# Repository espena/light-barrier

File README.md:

# Light barrier
Garage door light barrier. KiCad project with schematics and PCB layout. This project is shared under GNU general public license version 3, and is provided "as is", with no warranties what so ever. Use this material completely at your own risk.

## Transmitter circuit

| Component ID  | Type           | Description                    | Value  |
| ------------- |:---------------|:-------------------------------| ------:|
|  C1           | Capacitor      | Radial electrolytic, 10V       | 1000µF |
|  C2           | Capacitor      | Monolithic Ceramic Chip        |  470pF |
|  C3           | Capacitor      | Monolithic Ceramic Chip        |  100nF |
|  C4           | Capacitor      | Monolithic Ceramic Chip        |  100nF |
|  C5           | Capacitor      | Monolithic Ceramic Chip        |  100nF |
|  D1           | Diode          | 1N4001, 50V                    |     -  |
|  D2           | LED            | Green, 5mm                     |     -  |
|  D3           | IR-LED         | TSAL 6100                      |     -  |
|  J1           | Terminal block | KF128 2-pin, 5 mm pitch        |     -  |
| JP1           | Jumper         | 1x2 pin header with jumper     |     -  |
|  Q1           | Transistor     | BC338 NPN BJT                  |     -  |
|  R1           | Resistor       | Metal film, 1% tolerance       |    1kΩ |
|  R2           | Resistor       | Metal film, 1% tolerance       |   24kΩ |
|  R3           | Resistor       | Metal film, 1% tolerance       |  120kΩ |
|  R4           | Resistor       | Metal film, 1% tolerance       |   22kΩ |
|  R5           | Resistor       | Metal film, 1% tolerance       |  680kΩ |
|  R6           | Resistor       | Metal film, 1% tolerance       |   10kΩ |
|  R7           | Resistor       | Metal film, 1% tolerance       |  100kΩ |
|  R8           | Resistor       | Metal film, 1% tolerance       |   10Ω  |
| RV1           | Potentiometer  | Cermet 25-turn 3296W-1         |   10kΩ |
|  U1           | IC             | TLC555 timer circuit           |     -  |
|  U2           | IC             | TLC555 timer circuit           |     -  |

PCB layout for the transmitter is shared via
[OSH Park](https://oshpark.com/shared_projects/Knkobcg6)

## Receiver circuit

| Component ID  | Type           | Description                    | Value  |
| ------------- |:---------------|:-------------------------------| ------:|
|  C1           | Capacitor      | Radial electrolytic            |   47µF |
|  C2           | Capacitor      | Monolithic Ceramic Chip        |  100nF |
|  C3           | Capacitor      | Radial electrolytic            |   10µF |
|  C4           | Capacitor      | Monolithic Ceramic Chip        |  100nF |
|  C5           | Capacitor      | Monolithic Ceramic Chip        |  100nF |
|  C6           | Capacitor      | Monolithic Ceramic Chip        |  100nF |
|  C7           | Capacitor      | Radial electrolytic, 10V       | 1000µF |
|  D1           | Diode          | 1N4001, 50V                    |     -  |
|  D2           | Diode          | 1N4001, 50V                    |     -  |
|  D3           | LED            | Red, 5mm                       |     -  |
|  D4           | Diode          | 1N4001, 50V                    |     -  |
|  J1           | Terminal block | KF128 2-pin, 5 mm pitch        |     -  |
|  Q1           | Transistor     | BC557 PNP BJT                  |     -  |
|  Q2           | Transistor     | TIP120 darlington              |     -  |
|  R1           | Resistor       | Metal film, 1% tolerance       |  6,2kΩ |
|  R2           | Resistor       | Metal film, 1% tolerance       |   100Ω |
|  R3           | Resistor       | Metal film, 1% tolerance       |  100kΩ |
|  R4           | Resistor       | Metal film, 1% tolerance       |  100kΩ |
|  R5           | Resistor       | Metal film, 1% tolerance       |  6,8kΩ |
|  R6           | Resistor       | Metal film, 1% tolerance       |    1kΩ |
| RV1           | Potentiometer  | Cermet 25-turn 3296W-1         |  100kΩ |
| RV2           | Potentiometer  | Cermet 25-turn 3296W-1         |  100kΩ |
|  U1           | IC             | VS1838 IR receiver             |     -  |
|  U2           | IC             | TLC555 timer circuit           |     -  |
|  U3           | IC             | TLC555 timer circuit           |     -  |

PCB layout for the receiver is shared via
[OSH Park](https://oshpark.com/shared_projects/EA8wav7z)

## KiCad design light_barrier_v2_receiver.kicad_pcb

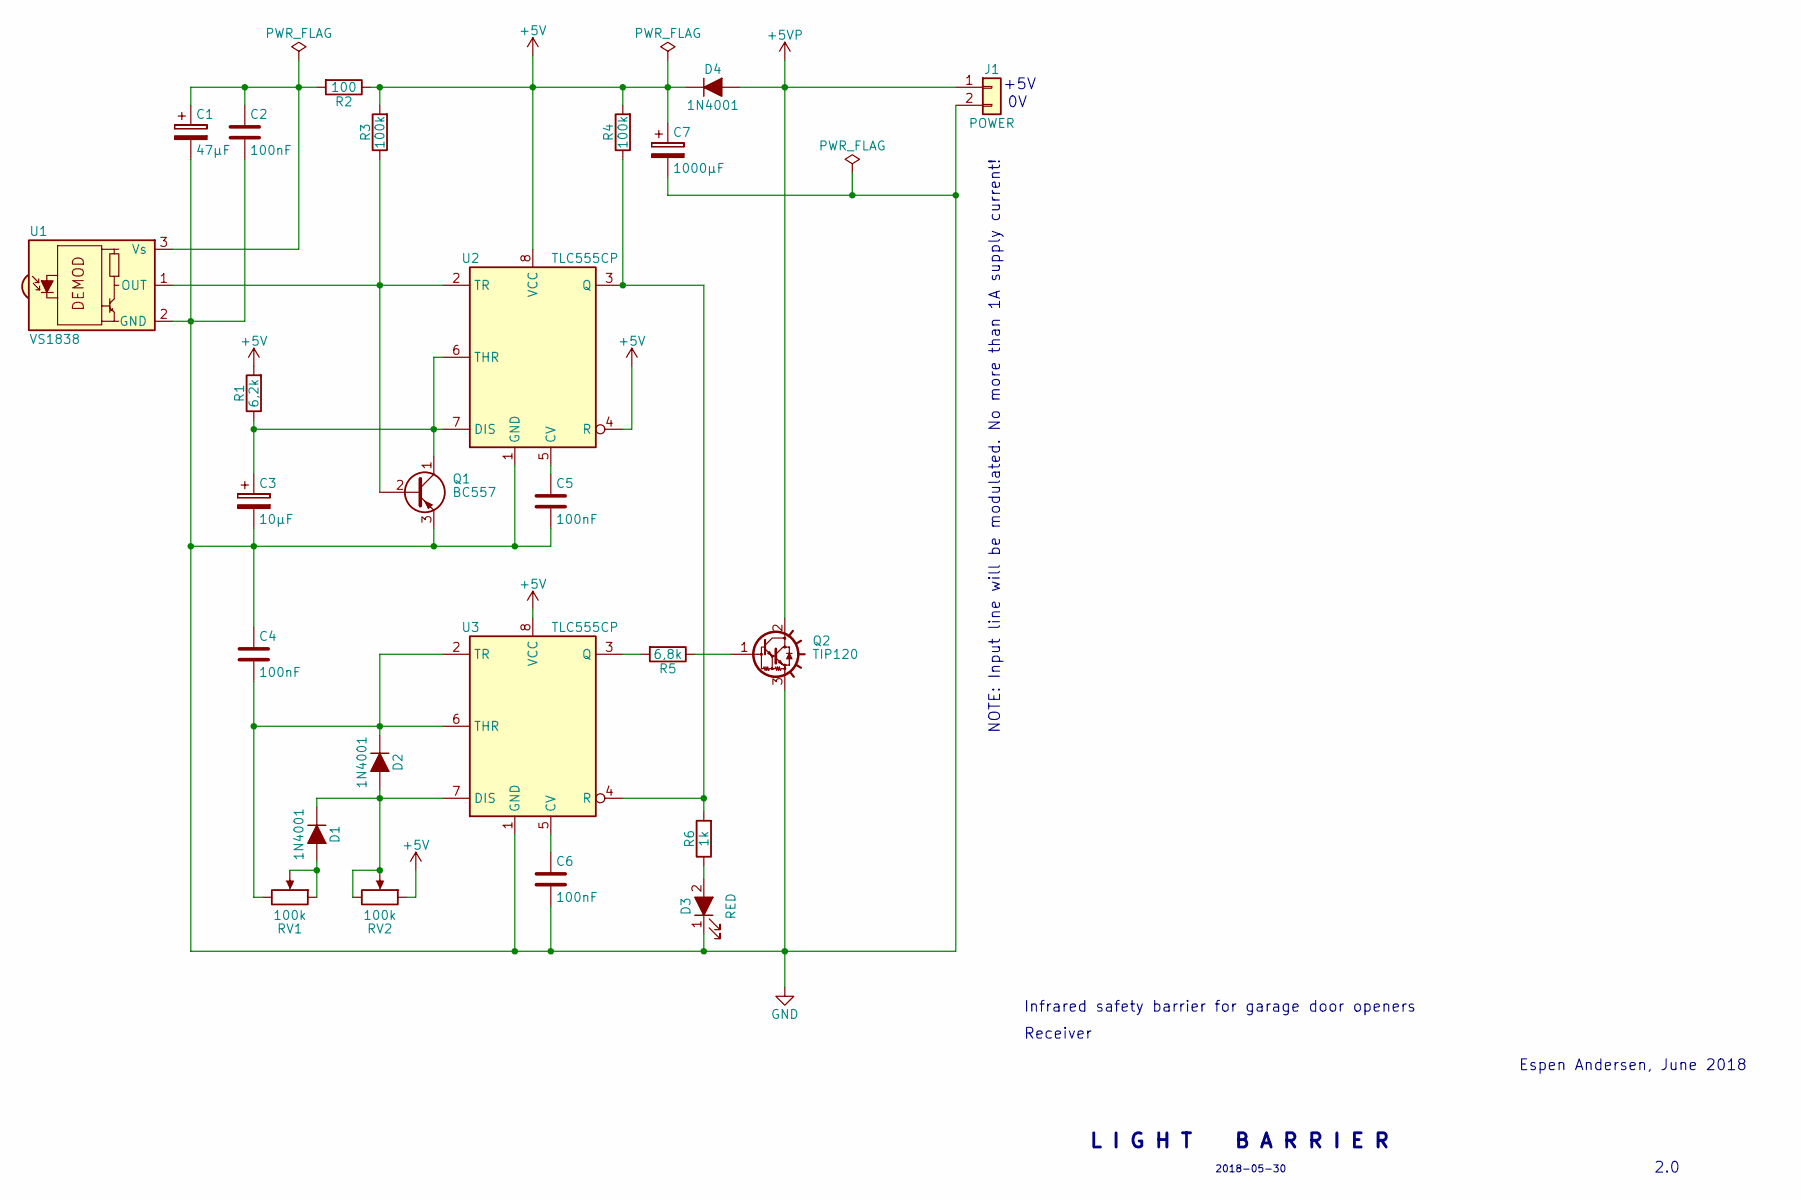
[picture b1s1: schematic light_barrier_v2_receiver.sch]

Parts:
C1: 47µF; CP_Radial_D4.0mm_P2.00mm
C2, C4, C5, C6: 100nF; C_Disc_D4.3mm_W1.9mm_P5.00mm
C3: 10µF; CP_Radial_D4.0mm_P2.00mm
C7: 1000µF; CP_Radial_D12.5mm_P5.00mm
D1, D2: 1N4001; D_DO-41_SOD81_P2.54mm_Vertical_KathodeUp
D3: RED; LED_D5.0mm
D4: 1N4001; D_DO-41_SOD81_P7.62mm_Horizontal
J1: POWER; TerminalBlock_Phoenix_PT-3.5mm_2pol
Q1: BC557; TO-92_Molded_Narrow_Oval
Q2: TIP120; TO-220-3_Vertical
R1: 6,2k; R_Axial_DIN0207_L6.3mm_D2.5mm_P2.54mm_Vertical
R2: 100; R_Axial_DIN0207_L6.3mm_D2.5mm_P7.62mm_Horizontal
R3, R4: 100k; R_Axial_DIN0207_L6.3mm_D2.5mm_P2.54mm_Vertical
R5: 6,8k; R_Axial_DIN0207_L6.3mm_D2.5mm_P2.54mm_Vertical
R6: 1k; R_Axial_DIN0207_L6.3mm_D2.5mm_P2.54mm_Vertical
RV1, RV2: 100k; Potentiometer_Trimmer_Bourns_3296W
U1: VS1838; IRReceiver_Vishay_MINICAST-3pin
U2, U3: TLC555CP; DIP-8_W7.62mm_LongPads

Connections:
+5V: C7.1, D4.1 (K), R1.2, R2.1, R3.2, R4.2, RV2.1, U2.4 (R), U2.8 (VCC), U3.8 (VCC)
+5VP: D4.2 (A), J1.1, Q2.2 (C)
GND: C1.2, C2.2, C3.2, C4.1, C5.2, C6.2, C7.2, D3.1 (K), J1.2, Q1.3 (E), Q2.3 (E), U1.2 (GND), U2.1 (GND), U3.1 (GND)
unnamed: C1.1, C2.1, R2.2, U1.3 (Vs)
unnamed: C3.1, Q1.1 (C), R1.1, U2.6 (THR), U2.7 (DIS)
unnamed: C4.2, D2.1 (K), RV1.3, U3.2 (TR), U3.6 (THR)
unnamed: C5.1, U2.5 (CV)
unnamed: C6.1, U3.5 (CV)
unnamed: D1.1 (K), D2.2 (A), RV2.2, RV2.3, U3.7 (DIS)
unnamed: D1.2 (A), RV1.1, RV1.2
unnamed: D3.2 (A), R6.1
unnamed: Q1.2 (B), R3.1, U1.1 (OUT), U2.2 (TR)
unnamed: Q2.1 (B), R5.1
unnamed: R4.1, R6.2, U2.3 (Q), U3.4 (R)
unnamed: R5.2, U3.3 (Q)

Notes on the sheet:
L I G H T B A R R I E R
Espen Andersen, June 2018
2018-05-30
2.0
Infrared safety barrier for garage door openers
+5V
Receiver
NOTE: Input line will be modulated. No more than 1A supply current!

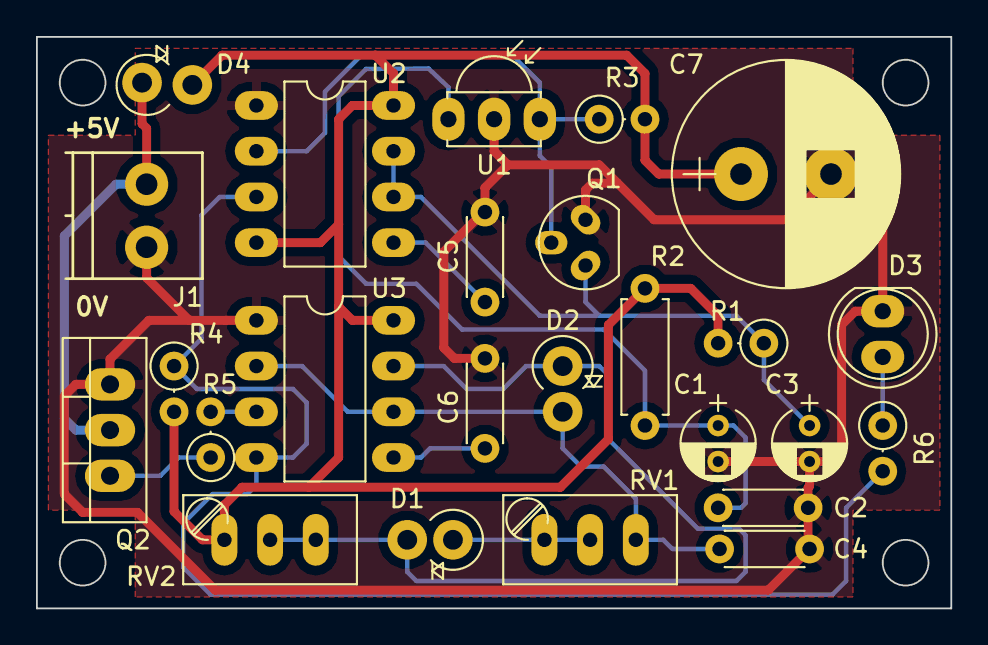
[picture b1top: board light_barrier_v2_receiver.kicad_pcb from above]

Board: 2 copper layers, 50.8 x 31.8 mm, 25 parts (0 on the bottom side), 15 nets.

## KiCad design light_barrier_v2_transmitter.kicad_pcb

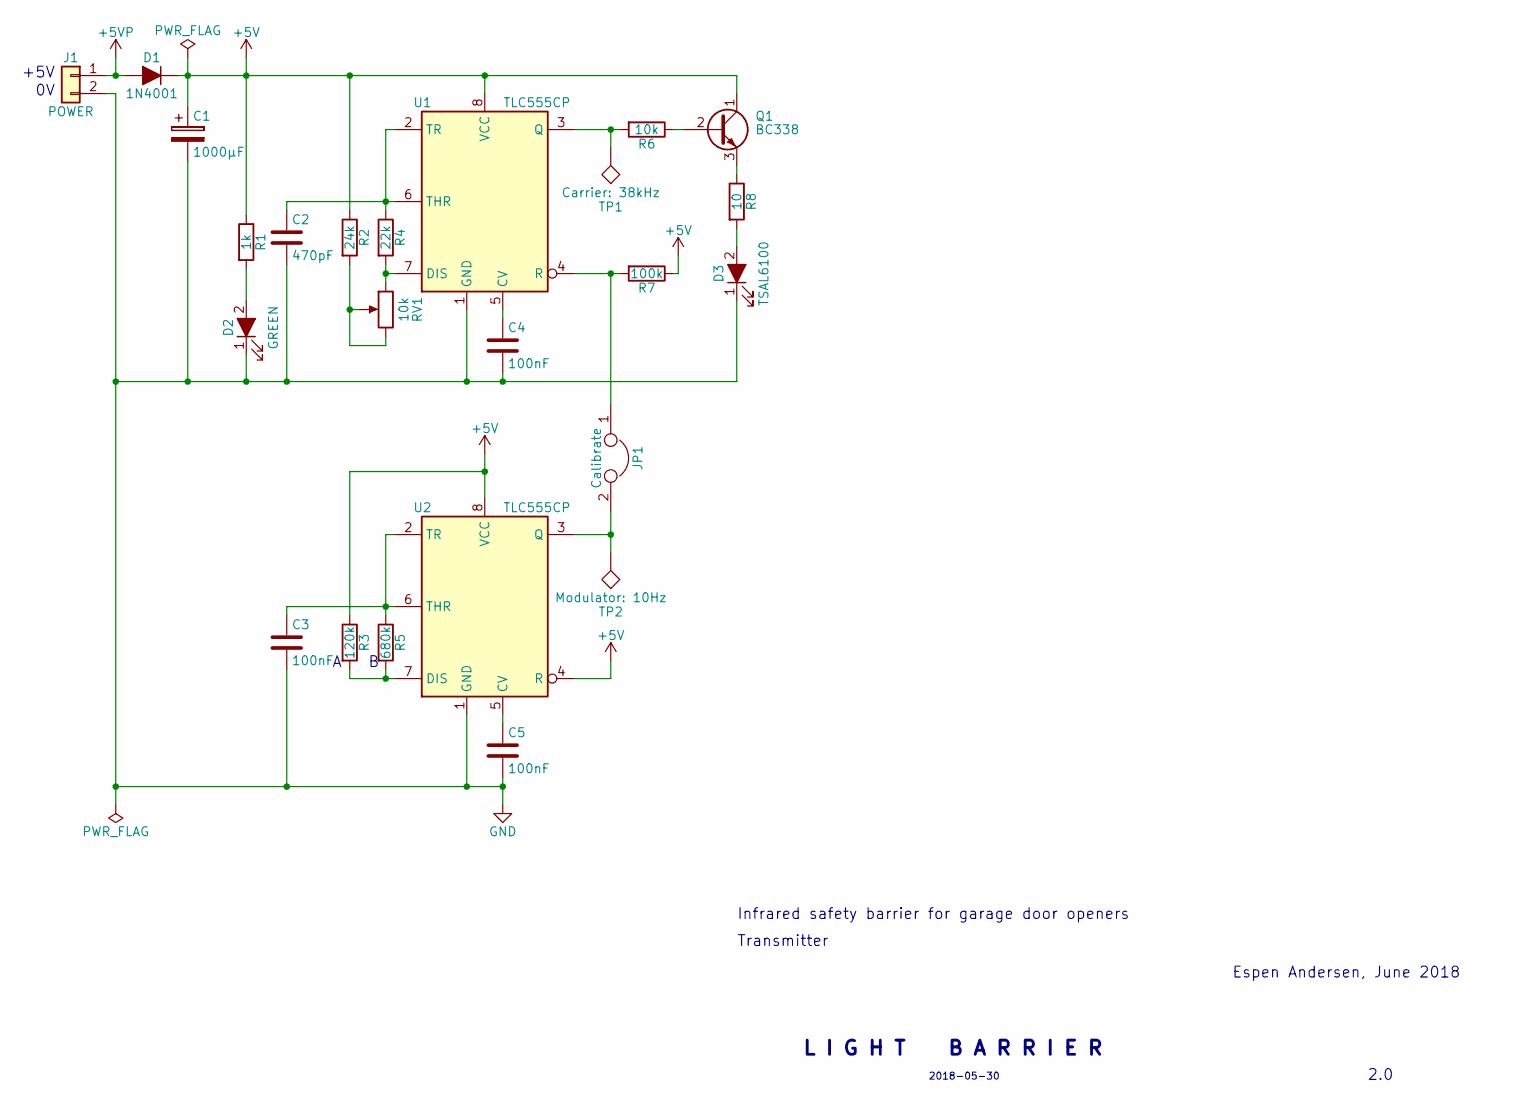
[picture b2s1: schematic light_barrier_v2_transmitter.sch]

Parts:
C1: 1000µF; CP_Radial_D12.5mm_P5.00mm
C2: 470pF; C_Disc_D4.3mm_W1.9mm_P5.00mm
C3, C4, C5: 100nF; C_Disc_D4.3mm_W1.9mm_P5.00mm
D1: 1N4001; D_DO-41_SOD81_P7.62mm_Horizontal
D2: GREEN; LED_D5.0mm
D3: TSAL6100; LED_D5.0mm
J1: POWER; Socket_Strip_Straight_1x02_Pitch2.54mm
JP1: Calibrate; Pin_Header_Straight_1x02_Pitch2.54mm
Q1: BC338; TO-92_Molded_Narrow
R1: 1k; R_Axial_DIN0207_L6.3mm_D2.5mm_P2.54mm_Vertical
R2: 24k; R_Axial_DIN0207_L6.3mm_D2.5mm_P2.54mm_Vertical
R3: 120k; R_Axial_DIN0207_L6.3mm_D2.5mm_P2.54mm_Vertical
R4: 22k; R_Axial_DIN0207_L6.3mm_D2.5mm_P2.54mm_Vertical
R5: 680k; R_Axial_DIN0207_L6.3mm_D2.5mm_P2.54mm_Vertical
R6: 10k; R_Axial_DIN0207_L6.3mm_D2.5mm_P2.54mm_Vertical
R7: 100k; R_Axial_DIN0207_L6.3mm_D2.5mm_P2.54mm_Vertical
R8: 10; R_Axial_DIN0207_L6.3mm_D2.5mm_P2.54mm_Vertical
RV1: 10k; Potentiometer_Trimmer_Bourns_3296W
TP1: Carrier: 38kHz; 1pin
TP2: Modulator: 10Hz; 1pin
U1, U2: TLC555CP; DIP-8_W7.62mm_LongPads

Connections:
+5V: C1.1, D1.1 (K), Q1.1 (C), R1.1, R2.1, R3.1, R7.1, U1.8 (VCC), U2.4 (R), U2.8 (VCC)
+5VP: D1.2 (A), J1.1
GND: C1.2, C2.2, C3.2, C4.2, C5.2, D2.1 (K), D3.1 (K), J1.2, U1.1 (GND), U2.1 (GND)
unnamed: C2.1, R4.1, U1.2 (TR), U1.6 (THR)
unnamed: C3.1, R5.1, U2.2 (TR), U2.6 (THR)
unnamed: C4.1, U1.5 (CV)
unnamed: C5.1, U2.5 (CV)
unnamed: D2.2 (A), R1.2
unnamed: D3.2 (A), R8.2
unnamed: JP1.1, R7.2, U1.4 (R)
unnamed: JP1.2, TP2.1, U2.3 (Q)
unnamed: Q1.2 (B), R6.1
unnamed: Q1.3 (E), R8.1
unnamed: R2.2, RV1.2, RV1.3
unnamed: R3.2, R5.2, U2.7 (DIS)
unnamed: R4.2, RV1.1, U1.7 (DIS)
unnamed: R6.2, TP1.1, U1.3 (Q)

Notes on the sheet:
L I G H T B A R R I E R
Espen Andersen, June 2018
2018-05-30
2.0
Infrared safety barrier for garage door openers
+5V
Transmitter

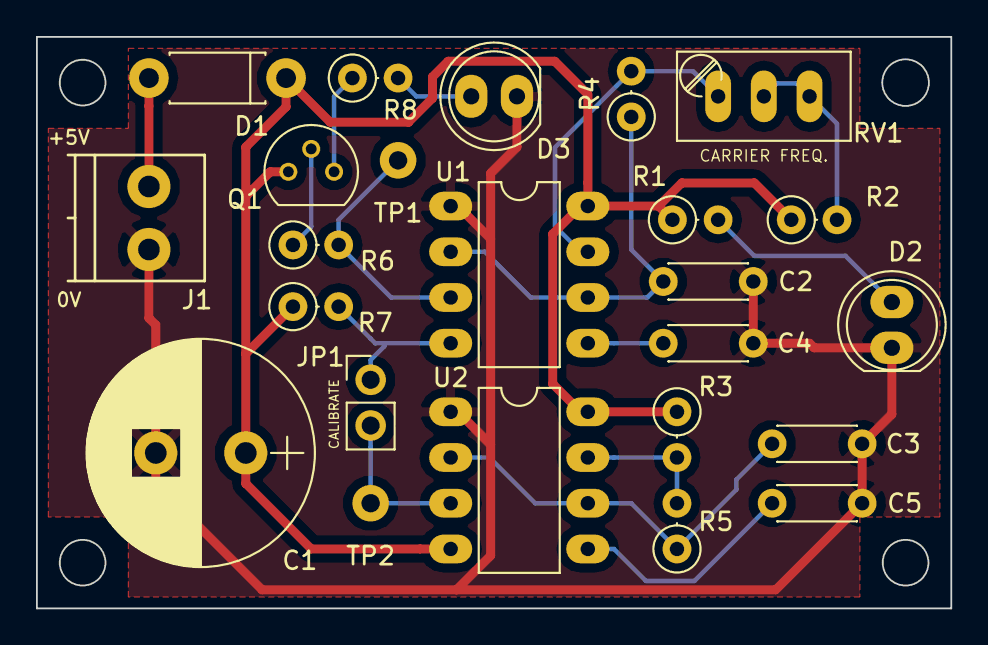
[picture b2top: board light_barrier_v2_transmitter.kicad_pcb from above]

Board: 2 copper layers, 50.8 x 31.8 mm, 24 parts (0 on the bottom side), 17 nets.

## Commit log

2018-07-09 Added warning to schematics
2018-07-12 Add parts list for transmitter.
2018-07-12 Amend parts list
2018-07-12 Add links to shared PCB layout.
2018-07-12 Add disclaimer.
